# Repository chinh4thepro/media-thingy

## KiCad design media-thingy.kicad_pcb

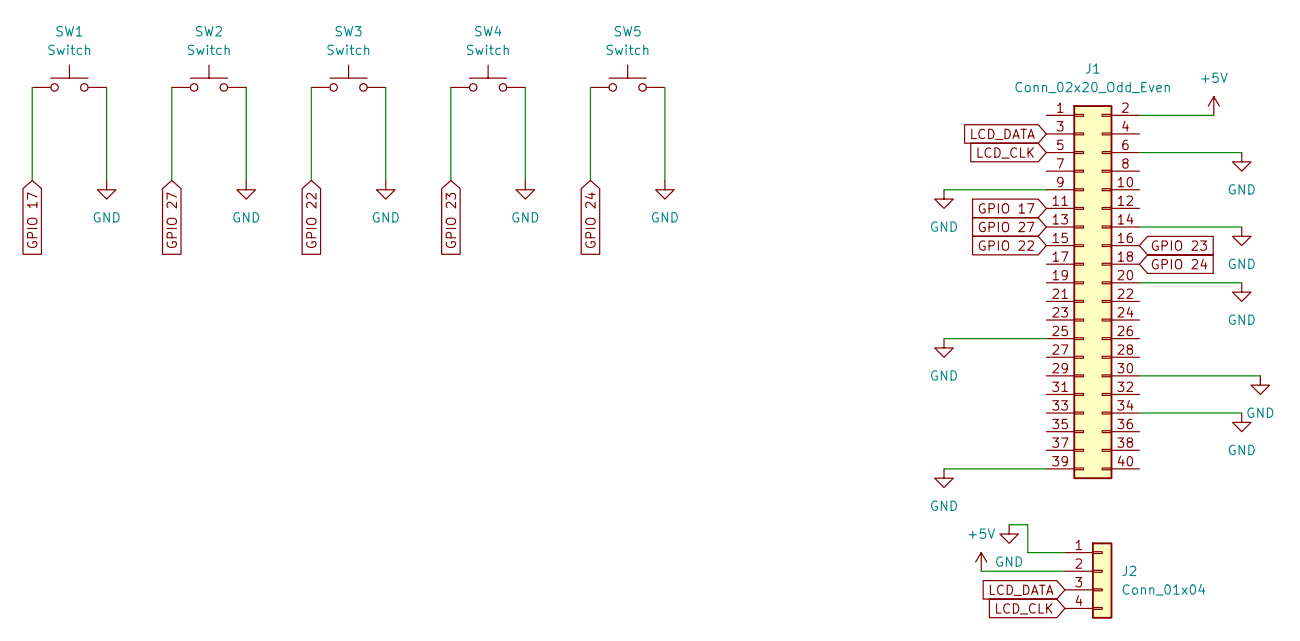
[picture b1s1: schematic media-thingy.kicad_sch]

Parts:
J1: Conn_02x20_Odd_Even; PinSocket_2x20_P2.54mm_Vertical
J2: Conn_01x04; PinSocket_1x04_P2.54mm_Vertical
SW1, SW2, SW3, SW4, SW5: Switch; Hotswap_MX

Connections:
+5V: J1.2, J2.2
GND: J1.6, J1.9, J1.14, J1.20, J1.25, J1.30, J1.34, J1.39, J2.1, SW1.2, SW2.2, SW3.2, SW4.2, SW5.2
GPIO 17: J1.11, SW1.1
GPIO 22: J1.15, SW3.1
GPIO 23: J1.16, SW4.1
GPIO 24: J1.18, SW5.1
GPIO 27: J1.13, SW2.1
LCD_CLK: J1.5, J2.4
LCD_DATA: J1.3, J2.3

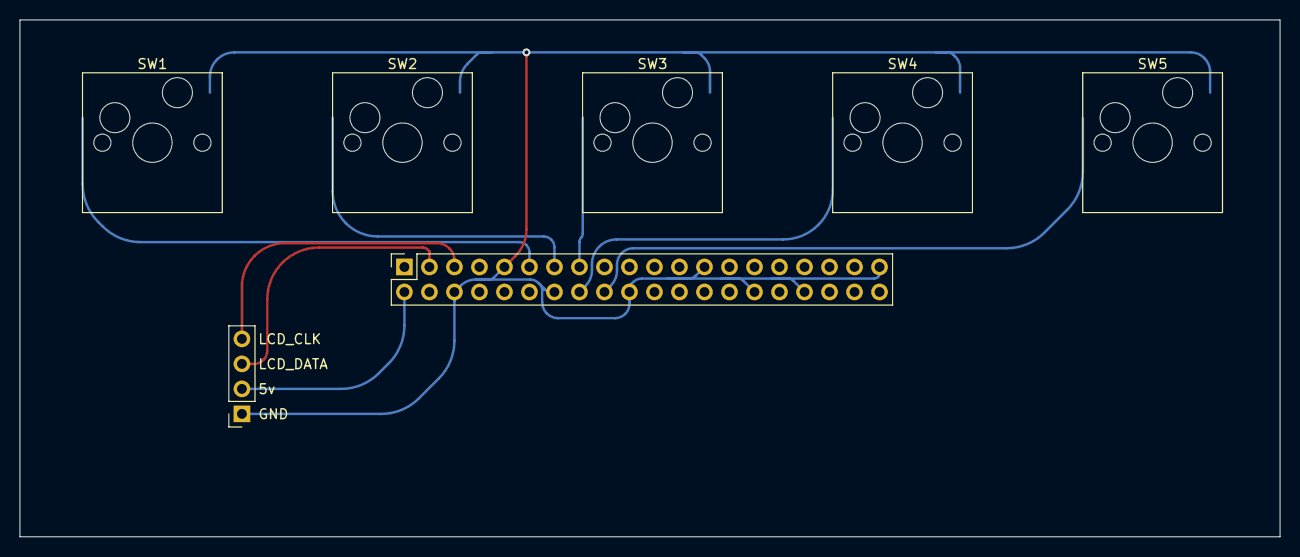
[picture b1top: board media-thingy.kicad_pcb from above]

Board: 2 copper layers, 128.0 x 52.5 mm, 7 parts (0 on the bottom side), 9 nets.

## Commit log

2024-07-21 remove unneeded files
2024-07-21 remove more unneeded stuff
2024-07-21 remove autosave
2024-07-21 update gitignore
2024-07-21 correct header sizes
2024-07-22 complete pcb
2024-07-24 fix distance between switches and edge
